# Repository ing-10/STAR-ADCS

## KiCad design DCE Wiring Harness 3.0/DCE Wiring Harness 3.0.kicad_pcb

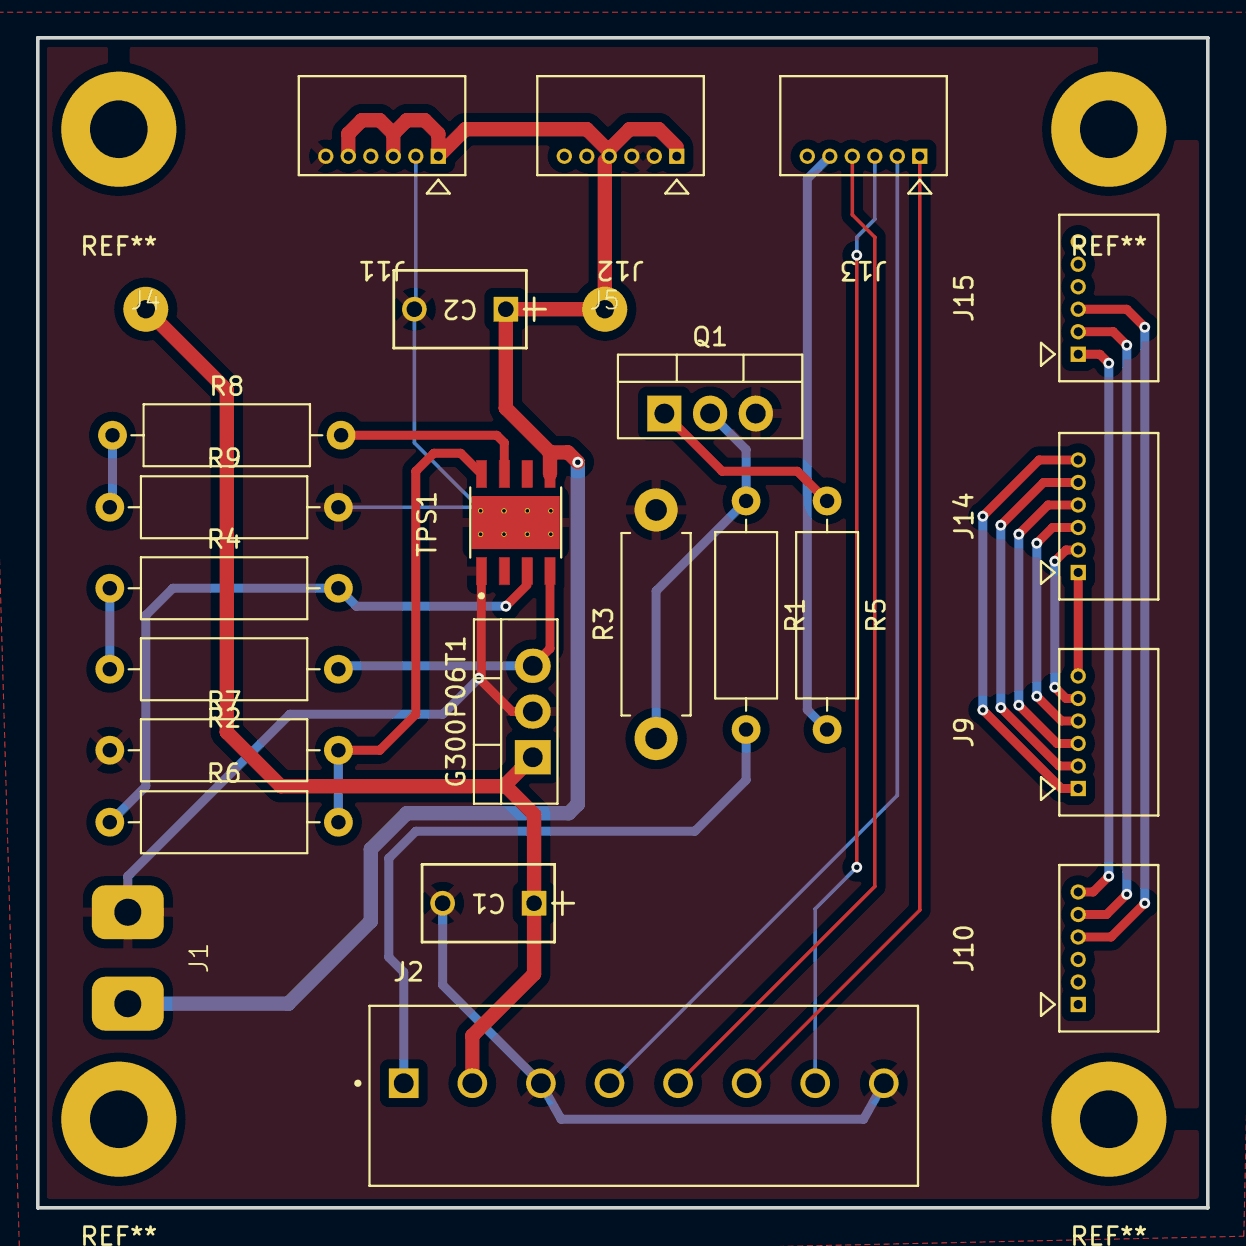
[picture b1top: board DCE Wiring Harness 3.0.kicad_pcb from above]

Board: 2 copper layers, 65.0 x 65.0 mm, 25 parts (0 on the bottom side), 26 nets.

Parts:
C1: C330C105K5R5TA; CAP_C330C_MR_X7R_KEM
C2: C330C105K5R5TA7301; CAP_C330C_MR_X7R_KEM
G300P06T1: PMOS; TO-220-3_Vertical
J1: Conn_01x02_Pin; Custom Test Pads
J2: 1728349; PHOENIX_1728349
J4, J5: Conn_01x01_Socket; jumper
J9, J10, J11, J12, J13, J14, J15: 530480610; CON_530480610_MOL
Q1: NMOS; TO-220-3_Vertical
R1, R5: 100; R_Axial_DIN0309_L9.0mm_D3.2mm_P12.70mm_Horizontal
R2: 10000; R_Axial_DIN0309_L9.0mm_D3.2mm_P12.70mm_Horizontal
R3: 1000; R_Axial_DIN0411_L9.9mm_D3.6mm_P12.70mm_Horizontal
R4: 560; R_Axial_DIN0309_L9.0mm_D3.2mm_P12.70mm_Horizontal
R6: 68; R_Axial_DIN0309_L9.0mm_D3.2mm_P12.70mm_Horizontal
R7: 1000; R_Axial_DIN0309_L9.0mm_D3.2mm_P12.70mm_Horizontal
R8: 680; R_Axial_DIN0309_L9.0mm_D3.2mm_P12.70mm_Horizontal
R9: 120; R_Axial_DIN0309_L9.0mm_D3.2mm_P12.70mm_Horizontal
TPS1: VREG_LM5017MR_NOPB

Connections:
+12V: C2.1, J1.1, J5.1, J11.1, J11.3, J11.5, J12.1, J12.4, TPS1.5 (OUT)
+12VA: C1.1, G300P06T1.1 (D), J2.02, J4.1
/3.3V GPIO: J2.01, R1.2
/+3.3VDC: J10.6, J15.1
/HA: J9.5, J14.2
/HB: J9.3, J14.4
/HC: J9.1, J14.6
/MOT_TEMP: J10.4, J15.3
/OUTA: J9.6, J14.1
/OUTB: J9.4, J14.3
/OUTC: J9.2, J14.5
/PWR_EN: J13.5, R5.2
/RXD+: J2.07, J13.3
/RXD-: J2.06, J13.1
/TXD+: J2.05, J13.4
/TXD-: J2.04, J13.2
GND: C1.2, C2.2, G300P06T1.2 (G), J1.2, J2.03, J2.08, J11.2, J11.4, J11.6, J12.2, J12.3, J12.5, Q1.3 (S), R3.2, R7.1, R9.2, TPS1.1 (GND), TPS1.9 (GND)
GND1: J10.3, J10.5, J15.2
unnamed: G300P06T1.3 (S), R2.1, TPS1.4 (IN)
unnamed: Q1.1 (D), R5.1
unnamed: Q1.2 (G), R1.1, R3.1
unnamed: R2.2, R4.1
unnamed: R8.1, R9.1
unnamed: R4.2, R6.1, TPS1.3 (EN/UVLO)
unnamed: R8.2, TPS1.7 (ILM)
unnamed: R6.2, R7.2, TPS1.8 (OVLO/OVCSEL)
